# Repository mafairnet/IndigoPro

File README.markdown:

## IndigoPro
============

A Set of Open Source Alarms based on Open Source Hardware.. 

[Source](http://github.com/mafairnet/IndigoPro)

### Features:
---------

- To be assigned.

### What's new:
---------

- Added Mark 3 to TWRB2 M3, includes capability to VoIP phone notifications.
- Renamed the Git to IndigoPro last known as (twrb2mini).
- Reorganized the project into sets (TWRB1 and TWRB2 each one composed by marks of it's generation ex. Mark1, Mark2, ..., MarkN).

### History
-------

### 0.0.1 ###

- Initial Pre-Release

### License
-------

Dual licensed under the MIT and GPL licenses:

*  [http://www.opensource.org/licenses/mit-license.php](http://www.opensource.org/licenses/mit-license.php)
*  [http://www.gnu.org/licenses/gpl.html](http://www.gnu.org/licenses/gpl.html)

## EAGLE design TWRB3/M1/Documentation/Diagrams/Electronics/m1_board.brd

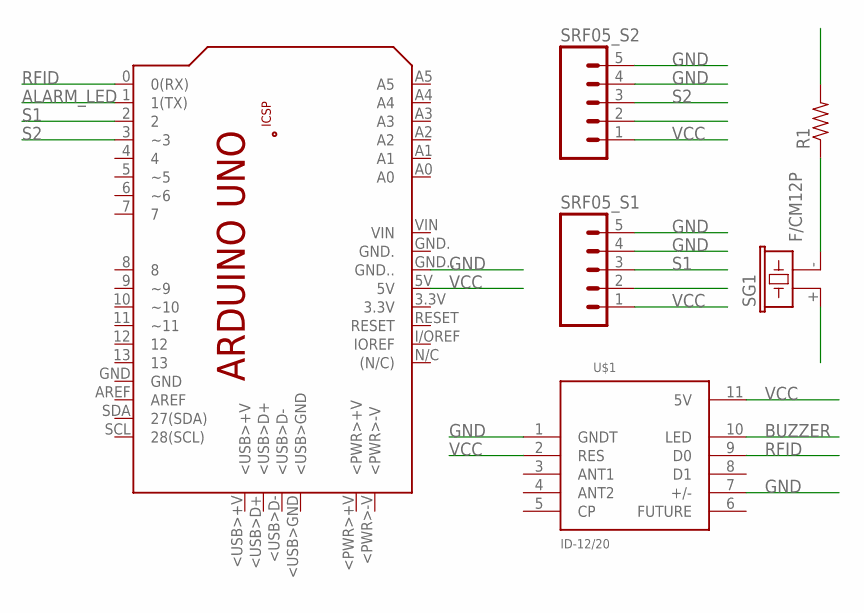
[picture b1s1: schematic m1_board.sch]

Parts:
PCB1: ARDUINO_UNO
R1: RESISTORPTH-1/4W; AXIAL-0.4
SG1: F/CM12P
SRF05_S1, SRF05_S2: M05PTH; 1X05
U$1: ID-12/20; ID-12

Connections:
ALARM_LED: PCB1.1 (1(TX))
BUZZER: R1.P$2 (2), U$1.10 (LED)
GND: PCB1.GND.., SRF05_S1.4, SRF05_S1.5, SRF05_S2.4, SRF05_S2.5, U$1.1 (GNDT), U$1.7 (+/-)
unnamed: R1.P$1 (1), SG1.- (2)
RFID: PCB1.0 (0(RX)), U$1.9 (D0)
S1: PCB1.2, SRF05_S1.3
S2: PCB1.3 (~3), SRF05_S2.3
VCC: PCB1.5V, SG1.+ (1), SRF05_S1.1, SRF05_S2.1, U$1.2 (RES), U$1.11 (5V)

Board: 2 copper layers, 6 parts (0 on the bottom side), 7 nets, no tracks yet.

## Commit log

2013-12-18 Initial notes
2014-02-07 Changed the couse of the project
    Added new reorganization and explanation of it.
2014-02-07 Readme Correction
    Changed classes to marks
2014-02-07 Added Documentation Docs
    Added documentation.
2014-03-21 Added PHP and Arduino Code
    Added code.
2014-04-18 Added TWRB3
    Added TWRB3
2014-05-01 Added TWRBX
2014-05-03 Updated README.markdown
2015-04-29 Added TWRB2 Mark 3
    Added initial files, documentation and configuration to the TWRB2 Mark 3
2015-04-30 Changes list updated
    Changes list updated
2017-11-17 Hola mundo

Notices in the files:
parts and their libraries:
SparkFun-Connectors: Licensing: CC v3.0 Share-Alike You are welcome to use this library for commercial purposes.
